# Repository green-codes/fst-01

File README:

Flying Stone Tiny 01 (FST-01SZ) PCB Design

							   Version 3.01
							     2018-12-11
						           Niibe Yutaka
						Flying Stone Technology

What's FST-01?
==============

Flying Stone Tiny 01 (FST-01) is a USB 32-bit computer by STM32 or
GD32 processor.  It has minimalist design.  It is composed by MCU
running at 72MHz or 108MHz, LED to notify a user, a hall effect sensor
for user input, and SWD port for main flash ROM update.  That's all.

This is designed mainly for our own projects: Gnuk and NeuG.

FST-01SZ is the third revision, integrating feedback from users.

MCU is new one from China.  Instead of offering extension I/O,
fixed-purpose sensor is added.  Optional flash memory is removed.

Please note that the format of KiCAD has been changed (again).

These files are for what?
=========================

This is FST-01 PCB design for KiCAD.

I am using kicad of 5.0.1+dfsg1-3 in Debian.

Files
=====

    README:      This file
    ChangeLog:   History of this project
    fst-01.pro:  Project file of KiCAD
    fst-01.sch:  Schematic
    fst-01.net:  Netlist
    fst-01.xml:  Component and Module
    fst-01.kicad_pcb:  PCB design
    library: schematic library
    module.pretty: footprint modules for PCB

    datasheet:   Datasheets of parts

Note that files under datasheet directory is copyrighted by vendors.

Terms and conditions
====================

FST-01 is my work, but I am not sure how and what I can demand for
users.  I think that PCB design and files can be copyrighted.

I assume that users don't use verbatim copy of this design.  It
includes my trade marks of "FST-01SZ" and Flying Stone logo.  Please
just don't include silk bottom layer, if you build your own PCB.

I would like to ask users to keep the design as "Open Hardware".  See
the archived page for the definition of "Open Hardware":

    https://web.archive.org/web/20140407171518/http://www.opencollector.org/Whyfree/open_hardware.html

That is, interface, design itself, and tools for the design should be
free.  Tools should be Free Software, in my opinion.  It is not enough
if tools are available by download with no cost.  Source code of tools
should be available and modification can be permitted.

Nevertheless, schematic design is distributed under the Creative
Commons Attribution 4.0 International License (CC BY 4.0).  See:

    https://creativecommons.org/licenses/by/4.0/

Schematic design can be used for any purpose and you don't need to
publish your modifications over my design.

For PCB, it is distributed under the Creative Commons
Attribution-ShareAlike 3.0 Unported (CC BY-SA 3.0).  See:

    https://creativecommons.org/licenses/by-sa/3.0/

External modules
================

The modules of module.pretty/c_0402.kicad_mod and
module.pretty/c_0603.kicad_mod was the one in the original file name
of module/SMT_CAP.mod in the version 1.00 of FST-01.

The module of module.pretty/r_0402.kicad_mod was module/SMT_RES.mod
in the version 1.00 of FST-01.

Those module drawings are copied from w_smd_cap.mod and
w_smd_resistors.mod by W.Lain.  Files were downloaded from:

   http://smisioto.no-ip.org/elettronica/kicad/kicad-en.htm

Its copyright notice is like following:
---------------------------------------------------------------------
Kicad Library by W. Lain - kcswalter@member.fsf.org

This library is released under the terms of the Creative Commons
license v3.0, Attribution-Share Alike.

The author holds no responsibility for any damage that can be caused
by the usage of this library. You are however welcome to report any
error or discrepance to the author, provided that you give also the
correct information and its source (i.e. the correct datasheet).

Note that the author used publicly available data sheets from many
different companies, and that package dimensions, pin numeration and
schematic symbols may vary slightly between companies.
---------------------------------------------------------------------
--

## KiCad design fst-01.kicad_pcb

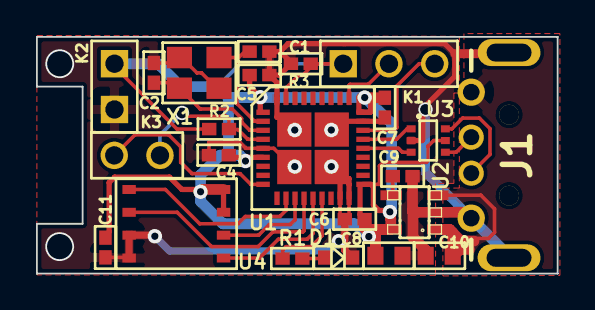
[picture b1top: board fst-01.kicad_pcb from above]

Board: 2 copper layers, 28.9 x 13.1 mm, 24 parts (1 on the bottom side), 21 nets.

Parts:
C1, C2: 27pF; c_0402
C4, C5, C6, C7, C11: 0.1uF; c_0402
C8, C10: 4.7uF; c_0603
C9: 0.01uF; c_0402
D1: LED; LED0603
J1: USB_A; USB-A-PLUG
JP1: Jumper_2_Open; SolderJumper-2_P1.3mm_Open_TrianglePad1.0x1.5mm
K1: K1; SIL-3-2
K2: K2; SIL-2-0
K3: K3; SIL-2-2
R1, R2, R3: 510; r_0402
U1: GD32F103TB; QFN36
U2: LP2985-33DBVR; SOT23-5
U3: NUF2221W1; SOT363
U4: SST25VF032B; WSON8
X1: 12MHz; ABM8G

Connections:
+3V3: C4.2, C5.2, C6.2, C7.2, C8.1, C11.2, JP1.1, K2.2, R2.2, U1.1, U1.6, U1.19, U1.27, U2.5, U3.5, U4.7, U4.8
/BOOT0: JP1.2, K1.1, R3.2, U1.35
/CLK: U1.12, U4.6
/D+: U1.24, U3.1
/D+_PLUG: J1.3, U3.6
/D-: U1.23, U3.3
/D-_PLUG: J1.2, U3.4
/LED: R1.2, U1.15
/MISO: U1.13, U4.2
/MOSI: U1.14, U4.5
/NRST: K3.1, R2.1, U1.4
/NSS: U1.11, U4.1
/OSC_IN: C1.1, U1.2, X1.1
/OSC_OUT: C2.1, U1.3, X1.2
/PA2: K3.2, U1.9
/SWCLK: K1.2, U1.28
/SWDIO: K1.3, U1.25
/VBUS: C10.1, J1.1, U2.1, U2.3
GND: C1.2, C2.2, C4.1, C5.1, C6.1, C7.1, C8.2, C9.2, C10.2, C11.1, D1.1, J1.4, J1.5, K2.1, R3.1, U1.5, U1.17, U1.18, U1.26, U1.36, U1.37, U2.2, U3.2, U4.3, U4.4, X1.3
unnamed: C9.1, U2.4
unnamed: D1.2, R1.1

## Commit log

2011-08-08 Add LQFP48 module
2011-08-08 added modules
2011-08-08 Add library
2011-08-08 Start using KiCAD
2011-08-08 name change of SIL-3-1.mod
2011-08-08 name change of SIL-3-2.mod
2011-08-08 name change of SIL-3-*.mod
2011-08-08 Start drawing
2011-08-09 draw PCB outline 13.5mm x 26mm
2011-08-10 Connect LED and R1
2011-08-10 Connect wires, fill zones
2011-08-10 Move references and values. Draw logo and product number.
2011-08-10 set plot parameters
2011-08-19 fix STF-202 connection
2011-08-22 fix logo
2011-08-23 Use NUF2221 instead of STF202
2011-08-26 move silks for references
2011-08-26 move silks for references (2)
2011-08-26 change silk of LED
2011-08-26 change capacitor module
2011-08-26 change resistor module
2011-08-26 change TSOT23-5 module
2011-08-26 README change
2011-08-26 change TSOT23-5 module (2)
2011-09-05 Fix NUF2221 connection
2011-09-06 minor change for silk
2011-09-06 fix Reference U3 size and position
2011-09-08 Pads Mask Clearance
2011-09-08 silk improvement
2011-09-09 Major change: QFN36
2011-09-12 improve small things
2011-09-12 QFN 37 pin solder paste improvement
2011-09-30 Change for SPI flash memory and small XTAL
2011-10-19 improvement a bit
2011-10-20 add FST-LOGO.mod
2011-10-20 silk outline move for ABM8G
2011-10-20 update PCB
2011-11-14 version 1.00
2016-06-08 board size change
2016-08-29 change +3V3 part in schematic.
2016-08-29 change parts of connectors
2016-08-29 fix connections of schematic
2016-08-29 fix direction of LED of schematic
2016-08-29 Fix schematic to FST-01G.
    * Make Serial flash ROM optional.
    * Connect USB connector's shield to GND.
    * Remove USB_EN control.
2016-08-29 change LDO to LP2985-33
2016-08-29 Add lp2985-n.pdf
2016-08-31 Add a footprint for newer KiCAD
2016-08-31 migrate footprint to newer KiCAD
2016-08-31 Fix LED direction
2016-08-31 Fix fp-lib-table
2016-08-31 add missing SOT363 footprint
2016-08-31 Fix footprints
2016-08-31 Update sch and net
2016-08-31 Update footprints
2016-08-31 Add xml
2016-08-31 Remove old files for older KiCAD
2016-08-31 Remove old footprints
2016-08-31 Add smd attr to footprint to generate POS
2016-08-31 fix U1 and U2
2016-08-31 update date
2016-08-31 Add WEEE-Logo from github/KiCad
2016-08-31 Add WEEE-logo
2016-08-31 Add generated files for the first version of FST-01G
2016-10-26 Version 2.00.
2018-08-08 fst-01sz.
2018-08-08 More change.
2018-08-08 Add hole sensor, drv5032.
2018-08-09 More change to PCBA.
2018-08-10 More changes.
2018-08-10 Add ordered files (including *.zip).
2018-08-11 change parts.
2018-08-11 Ask PCBA quote with this.
2018-08-13 Add position file and name change for U1 to GD.
2018-08-13 Add files for PCBA.
2018-08-16 Update PCBA.
2018-08-16 Update for the order of PCBA.
2018-08-16 Solder paste for J1 holes to be used to position stencil.
2018-08-20 Shape of PCB modified.
2018-08-23 Add datasheet for chips.
2018-09-25 Save Aug 16 order to o4.
2018-09-26 Order of 2018-09-26.
2018-09-26 Update just before the order.
2018-09-26 More change to order.
2018-11-19 Add info for BOM and order to fusion PCBA service on September 26.
2018-11-27 Version 3.00.
2018-12-04 Fix holes for J1 (distance is 10.40mm).
2018-12-05 Move output to o5.
2018-12-05 Add datasheet of ZL-271 and ZL-272.
2018-12-05 Fix J1 outlines.
2018-12-05 Add GND lines to central heat-pad.
2018-12-05 Add updated output/.
2018-12-11 Version 3.01.
2018-12-26 Add datasheet/ZL-272-variant.pdf.
2021-06-29 added & improved FST-01R design
2021-06-29 FST-01R rev1.1
2021-06-30 rev1.2; changed PA3 pad to NRST for easier debugging
2021-06-30 added boot0 support: both pin and jumper pad
2021-07-01 rev 1.3
2021-08-26 FST-01R design
